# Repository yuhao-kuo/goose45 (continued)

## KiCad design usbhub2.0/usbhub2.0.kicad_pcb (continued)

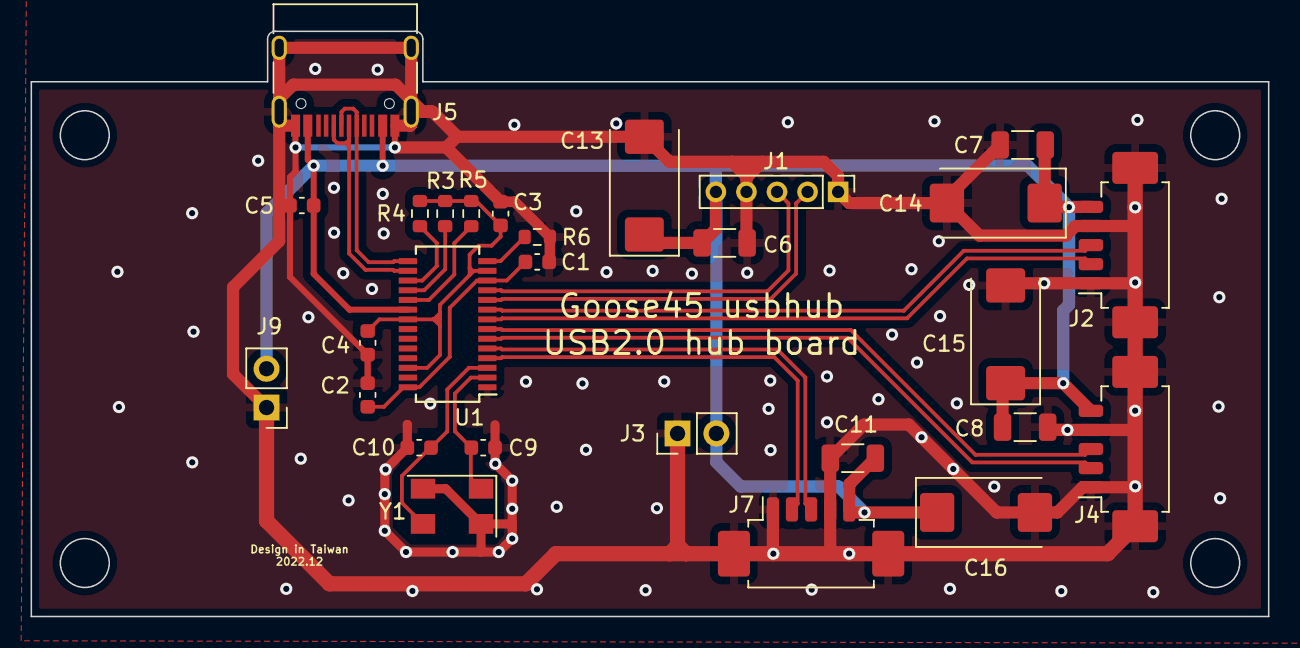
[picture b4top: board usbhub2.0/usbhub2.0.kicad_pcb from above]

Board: 2 copper layers, 81.0 x 38.3 mm, 28 parts (0 on the bottom side), 20 nets.

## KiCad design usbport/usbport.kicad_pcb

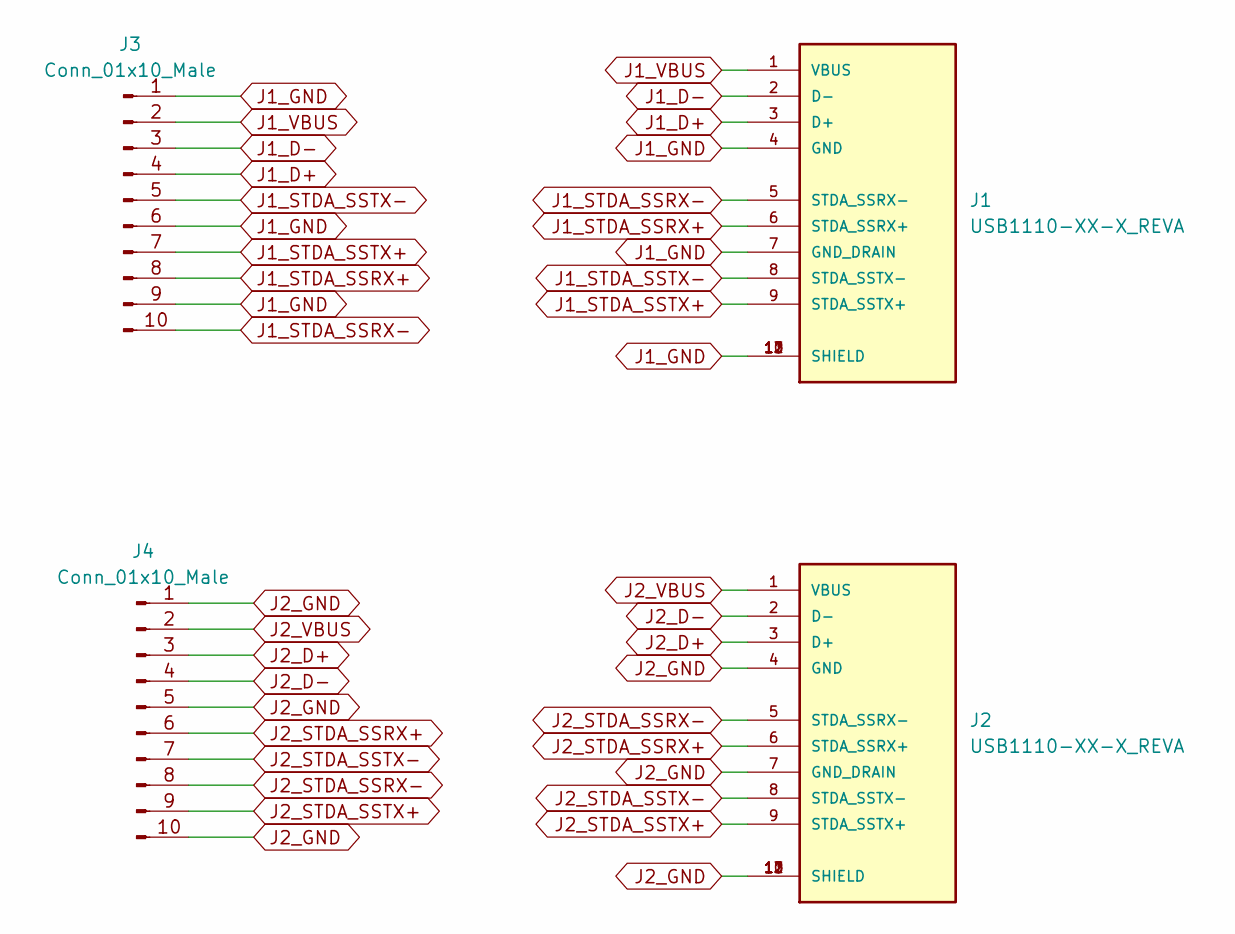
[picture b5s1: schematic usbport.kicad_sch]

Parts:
J1, J2: USB1110-XX-X_REVA; GCT_USB1110_goose45_usbport
J3, J4: Conn_01x10_Male; PinHeader_2x05_P2.00mm_Vertical

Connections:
J1_D+: J1.3 (D+), J3.4
J1_D-: J1.2 (D-), J3.3
J1_GND: J1.4 (GND), J1.7 (GND_DRAIN), J1.10 (SHIELD), J1.11 (SHIELD), J1.12 (SHIELD), J1.13 (SHIELD), J3.1, J3.6, J3.9
J1_STDA_SSRX+: J1.6 (STDA_SSRX+), J3.8
J1_STDA_SSRX-: J1.5 (STDA_SSRX-), J3.10
J1_STDA_SSTX+: J1.9 (STDA_SSTX+), J3.7
J1_STDA_SSTX-: J1.8 (STDA_SSTX-), J3.5
J1_VBUS: J1.1 (VBUS), J3.2
J2_D+: J2.3 (D+), J4.3
J2_D-: J2.2 (D-), J4.4
J2_GND: J2.4 (GND), J2.7 (GND_DRAIN), J2.10 (SHIELD), J2.11 (SHIELD), J2.12 (SHIELD), J2.13 (SHIELD), J4.1, J4.5, J4.10
J2_STDA_SSRX+: J2.6 (STDA_SSRX+), J4.6
J2_STDA_SSRX-: J2.5 (STDA_SSRX-), J4.8
J2_STDA_SSTX+: J2.9 (STDA_SSTX+), J4.9
J2_STDA_SSTX-: J2.8 (STDA_SSTX-), J4.7
J2_VBUS: J2.1 (VBUS), J4.2

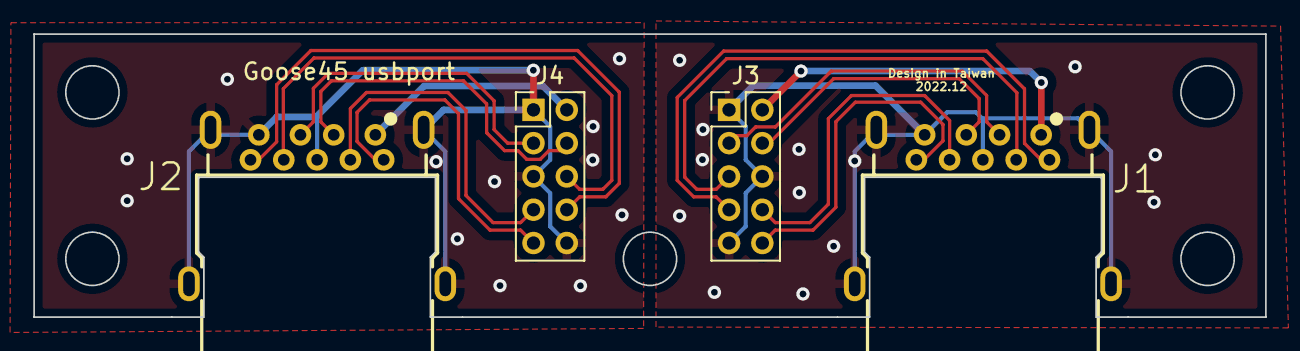
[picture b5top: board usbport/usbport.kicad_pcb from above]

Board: 2 copper layers, 74.0 x 17.0 mm, 4 parts (0 on the bottom side), 16 nets.

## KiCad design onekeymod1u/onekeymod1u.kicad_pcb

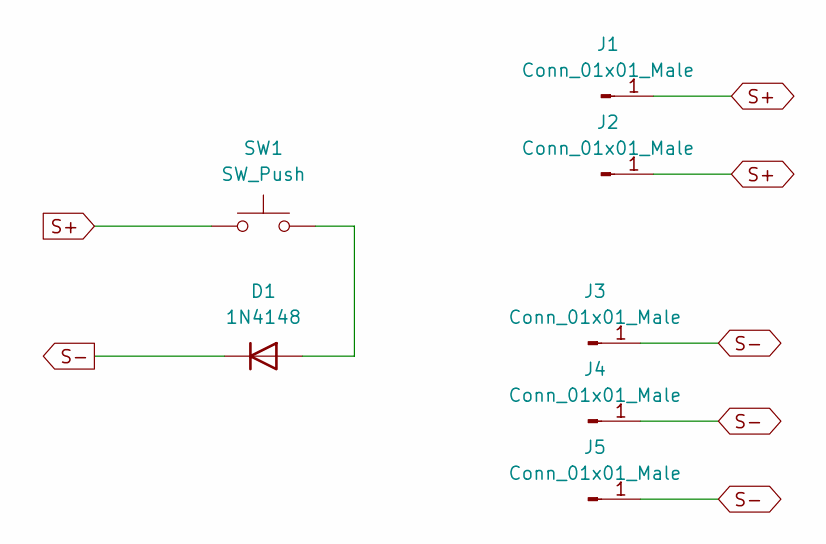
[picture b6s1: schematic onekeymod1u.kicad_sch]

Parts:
D1: 1N4148; D_SOD-323
J1, J2, J3, J4, J5: Conn_01x01_Male; PinSocket_1x01_P2.00mm_Vertical
SW1: SW_Push; SW_Hotswap_Kailh_MX

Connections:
unnamed: D1.2 (A), SW1.2
S+: J1.1, J2.1, SW1.1
S-: D1.1 (K), J3.1, J4.1, J5.1

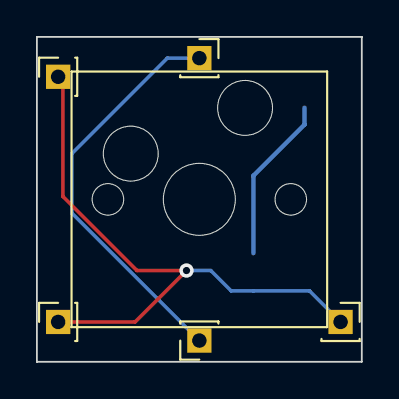
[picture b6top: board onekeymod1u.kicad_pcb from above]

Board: 2 copper layers, 18.0 x 18.0 mm, 7 parts (1 on the bottom side), 3 nets.

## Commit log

2022-07-27 Create License
2022-08-19 clean project
    * update sch from goose60
2022-08-20 update key switch location on pcb
2022-10-07 clean project
2022-10-07 add submodule keyswitch-kicad-library
2022-10-13 Update lib and rewrite PCB layout
2022-10-13 fix PCB GND issue
2022-10-14 update PCB layout
2022-10-15 add GND via and update PCB height
2022-10-16 move the PCB project to goose45rev1
2022-10-18 remove the usb conn on rev1
2022-10-19 update usb layout and add connector
2022-10-19 Add License
2022-10-19 update License
2022-10-22 change Diode pcb pad and modify usb connector location
2022-10-22 add README
2022-10-23 update 3D model
2022-11-04 update goose45 pcb usb pad and crystal
2022-11-10 add usbhub board
2022-11-12 add 1u key switch mod pcb board
2022-11-21 Change goose45 mod key size
2022-12-05 update pcb
2022-12-24 change usb2.0 hub board design
2022-12-24 change goose45 main board edge.cuts
2022-12-25 rename usbhub to usbhub2.0
2022-12-25 add usb 2.0 type-c board
2022-12-25 add usb port board
2022-12-26 change pcb thickness and add ubhc 3d step file
2022-12-30 change usbhub2.0 board design
    * remove usb molex input and add usb-c to input channel
    * change usbout1 molex to pin header
2022-12-31 update goose45 pcb board edge comment
    * goose45 - update board layout
    * usbport - change edge size and add edge comment
    * usbhub2.0 - change layout and the footprint
2023-01-13 update pcb common and update goose45 key loaction
2023-01-16 update usb type-c 3d model
2023-01-21 remove goose45 pcb usb type-c
2023-01-21 update goose45 pcb comments
2023-01-23 add goose45 case
2023-01-24 change goose45 pcb board edge
2023-01-24 update goose45 group cad
2023-02-04 update bottom case v6
2023-02-12 change goose45 power module foodpoint
2023-02-15 update goose45case version to v7
2023-03-04 update usbport pcb edge size comments
2023-03-04 update goose45case class usbport design
2023-03-30 modify the usbhub2.0 board edge
2023-04-01 Update case design to version 9
2023-04-01 update usbhub 2.0 board edge size and the comment
2023-05-23 update plate
2023-10-07 add goose45rev2 pcb
2023-12-04 add usbhub2.0 rev2
2023-12-09 add goose45 rev3 and usbhub2.3 rev2
2023-12-30 add goose45 case v10 and update sub-usb pcb
